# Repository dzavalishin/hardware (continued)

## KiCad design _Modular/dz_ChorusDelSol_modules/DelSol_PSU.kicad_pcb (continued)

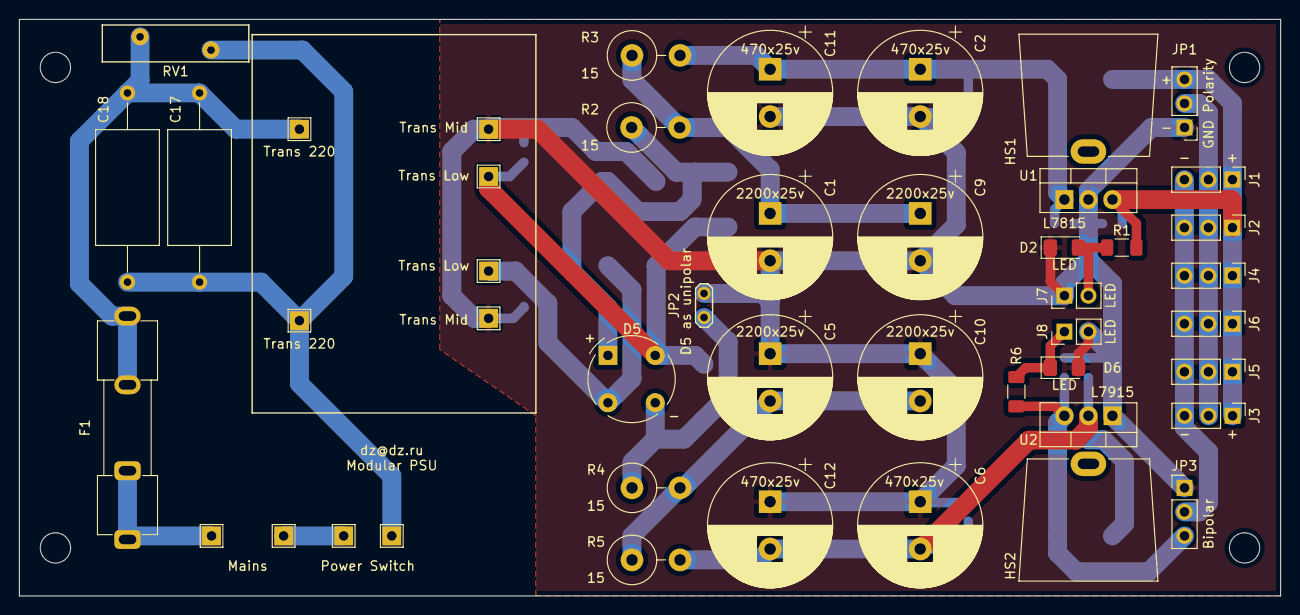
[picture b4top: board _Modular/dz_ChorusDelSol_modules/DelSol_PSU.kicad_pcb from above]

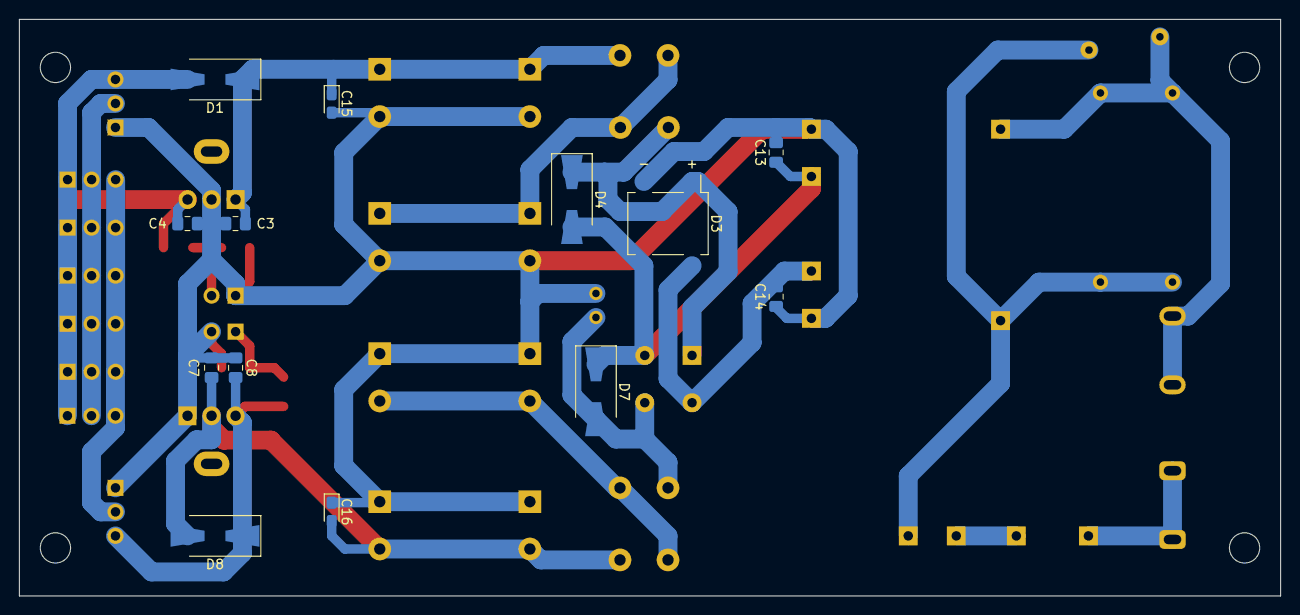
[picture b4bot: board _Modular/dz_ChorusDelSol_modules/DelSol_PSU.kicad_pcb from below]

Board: 2 copper layers, 133.3 x 61.0 mm, 63 parts (13 on the bottom side), 19 nets.

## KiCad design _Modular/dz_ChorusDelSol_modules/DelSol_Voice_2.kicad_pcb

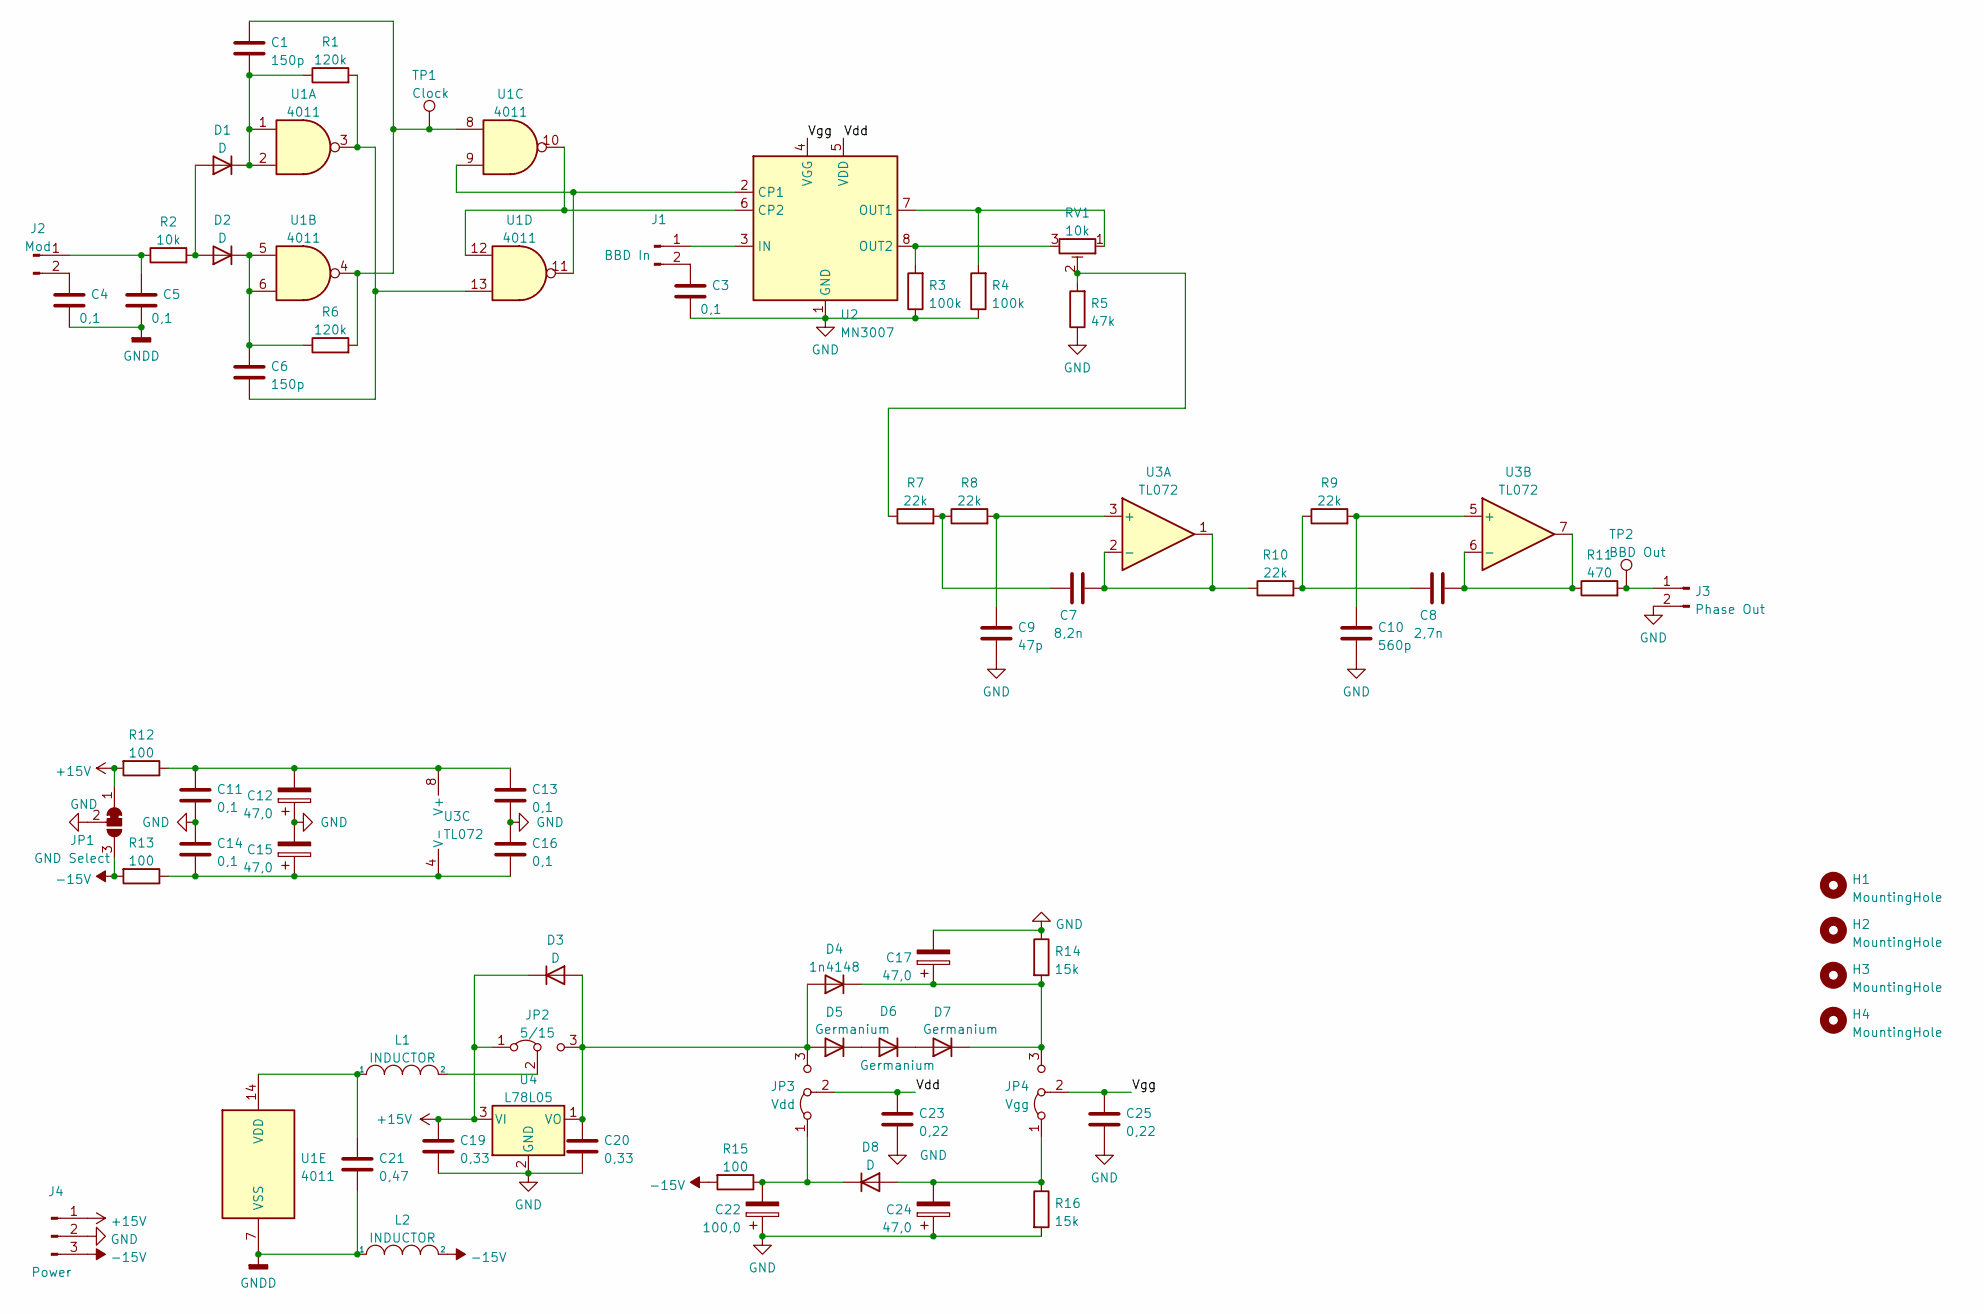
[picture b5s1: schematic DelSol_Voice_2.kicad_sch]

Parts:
C1, C6: 150p; C_Disc_D5.0mm_W2.5mm_P2.50mm
C3, C4, C5, C11, C13, C14, C16: 0,1; C_1206_3216Metric_Pad1.33x1.80mm_HandSolder
C7: 8,2n; C_Disc_D5.0mm_W2.5mm_P2.50mm
C8: 2,7n; C_Disc_D5.0mm_W2.5mm_P2.50mm
C9: 47p; C_Disc_D5.0mm_W2.5mm_P2.50mm
C10: 560p; C_Disc_D5.0mm_W2.5mm_P2.50mm
C12, C15, C17, C24: 47,0; C_Elec_6.3x5.8
C19, C20: 0,33; C_0805_2012Metric_Pad1.18x1.45mm_HandSolder
C21: 0,47; C_0805_2012Metric_Pad1.18x1.45mm_HandSolder
C22: 100,0; C_Elec_6.3x5.8
C23, C25: 0,22; C_0805_2012Metric_Pad1.18x1.45mm_HandSolder
D1, D2, D3, D8: D; D_MiniMELF_Handsoldering
D4: 1n4148; D_MiniMELF_Handsoldering
D5, D6, D7: Germanium; D_A-405_P2.54mm_Vertical_KathodeUp
H1, H2, H3, H4: MountingHole; MountingHole_3.2mm_M3
J1: BBD In; PinHeader_1x02_P2.54mm_Vertical
J2: Mod; PinHeader_1x02_P2.54mm_Vertical
J3: Phase Out; PinHeader_1x02_P2.54mm_Vertical
J4: Power; PinHeader_1x03_P2.54mm_Vertical
JP1: GND Select; PinHeader_1x03_P2.54mm_Vertical
JP2: 5/15; PinHeader_1x03_P2.54mm_Vertical
JP3: Vdd; PinHeader_1x03_P2.54mm_Vertical
JP4: Vgg; PinHeader_1x03_P2.54mm_Vertical
L1, L2: INDUCTOR; L_Radial_D10.0mm_P5.00mm_Fastron_07P
R1, R6: 120k; R_1206_3216Metric_Pad1.30x1.75mm_HandSolder
R2: 10k; R_1206_3216Metric_Pad1.30x1.75mm_HandSolder
R3, R4: 100k; R_1206_3216Metric_Pad1.30x1.75mm_HandSolder
R5: 47k; R_1206_3216Metric_Pad1.30x1.75mm_HandSolder
R7, R8, R9, R10: 22k; R_1206_3216Metric_Pad1.30x1.75mm_HandSolder
R11: 470; R_1206_3216Metric_Pad1.30x1.75mm_HandSolder
R12, R13, R15: 100; R_1206_3216Metric_Pad1.30x1.75mm_HandSolder
R14, R16: 15k; R_1206_3216Metric_Pad1.30x1.75mm_HandSolder
RV1: 10k; Potentiometer_Runtron_RM-065_Vertical
TP1: Clock; PinHeader_1x01_P2.54mm_Vertical
TP2: BBD Out; PinHeader_1x01_P2.54mm_Vertical
U1: 4011; DIP-14_W7.62mm
U2: MN3007; DIP-8_W7.62mm
U3: TL072; DIP-8_W7.62mm_Socket_LongPads
U4: L78L05; TO-92_Inline

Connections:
+15V: C19.1, D3.1 (K), J4.1, JP1.1 (A), JP2.1 (A), R12.2, U4.3 (VI)
-15V: J4.3, JP1.3 (B), L2.2, R13.2, R15.2
/Vdd: C23.1, JP3.2 (C), U2.5 (VDD)
/Vgg: C25.1, JP4.2 (C), U2.4 (VGG)
GND: C3.2, C9.1, C10.1, C11.2, C12.1, C13.2, C14.1, C15.2, C16.1, C17.2, C19.2, C20.2, C22.1, C23.2, C24.1, C25.2, J3.2, J4.2, JP1.2 (C), R3.1, R4.1, R5.1, R14.1, R16.2, U2.1 (GND), U4.2 (GND)
GNDD: C4.2, C5.2, C21.2, L2.1, U1.7 (VSS)
unnamed: C1.1, R6.2, TP1.1, U1.4, U1.8
unnamed: C1.2, D1.1 (K), R1.1, U1.1, U1.2
unnamed: C3.1, J1.2
unnamed: C4.1, J2.2
unnamed: C5.1, J2.1, R2.1
unnamed: C6.1, D2.1 (K), R6.1, U1.5, U1.6
unnamed: C6.2, R1.2, U1.3, U1.13
unnamed: C7.1, R7.2, R8.1
unnamed: C7.2, R10.1, U3.1, U3.2 (-)
unnamed: C8.1, R9.1, R10.2
unnamed: C8.2, R11.1, U3.6 (-), U3.7
unnamed: C9.2, R8.2, U3.3 (+)
unnamed: C10.2, R9.2, U3.5 (+)
unnamed: C11.1, C12.2, C13.1, R12.1, U3.8 (V+)
unnamed: C14.2, C15.1, C16.2, R13.1, U3.4 (V-)
unnamed: C17.1, D4.1 (K), D7.1 (K), JP4.3 (B), R14.2
unnamed: C20.1, D3.2 (A), D4.2 (A), D5.2 (A), JP2.3 (B), JP3.3 (B), U4.1 (VO)
unnamed: C21.1, L1.1, U1.14 (VDD)
unnamed: C22.2, D8.1 (K), JP3.1 (A), R15.1
unnamed: C24.2, D8.2 (A), JP4.1 (A), R16.1
unnamed: D1.2 (A), D2.2 (A), R2.2
unnamed: D5.1 (K), D6.2 (A)
unnamed: D6.1 (K), D7.2 (A)
unnamed: J1.1, U2.3 (IN)
unnamed: J3.1, R11.2, TP2.1
unnamed: JP2.2 (C), L1.2
unnamed: R3.2, RV1.3, U2.8 (OUT2)
unnamed: R4.2, RV1.1, U2.7 (OUT1)
unnamed: R5.2, R7.1, RV1.2
unnamed: U1.10, U1.12, U2.6 (CP2)
unnamed: U1.9, U1.11, U2.2 (CP1)

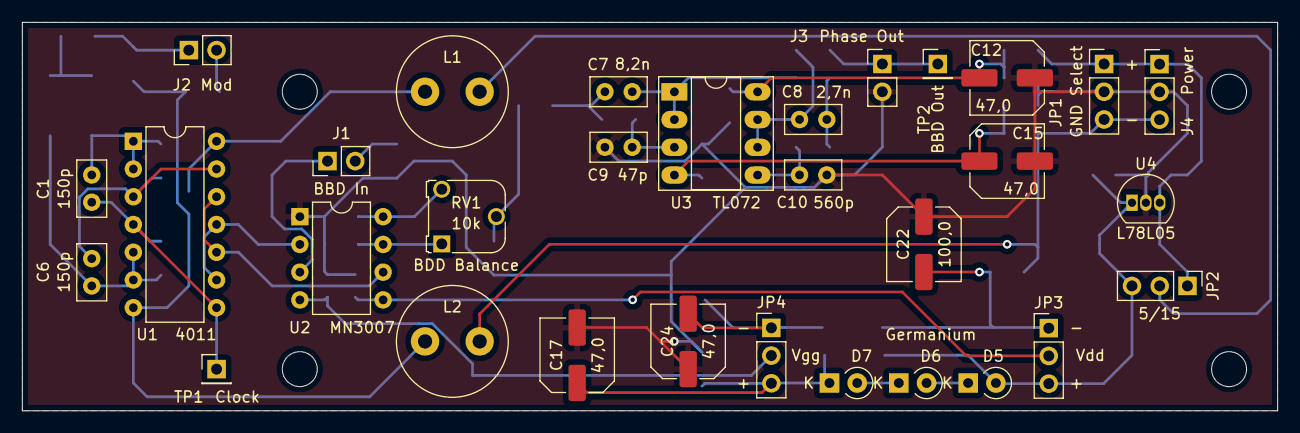
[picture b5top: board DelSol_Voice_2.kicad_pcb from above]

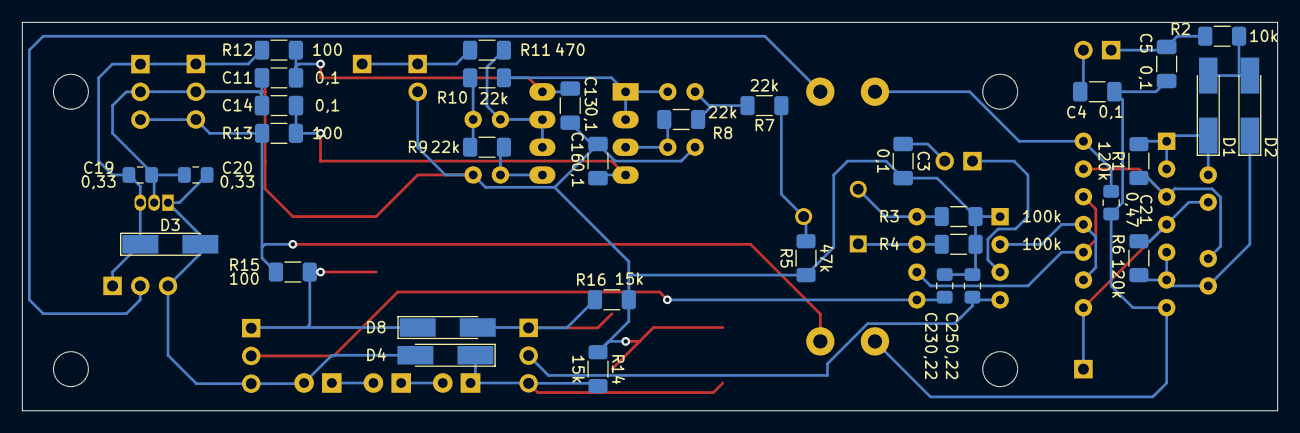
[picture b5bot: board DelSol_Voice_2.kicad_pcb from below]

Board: 2 copper layers, 114.9 x 35.6 mm, 68 parts (33 on the bottom side), 37 nets.

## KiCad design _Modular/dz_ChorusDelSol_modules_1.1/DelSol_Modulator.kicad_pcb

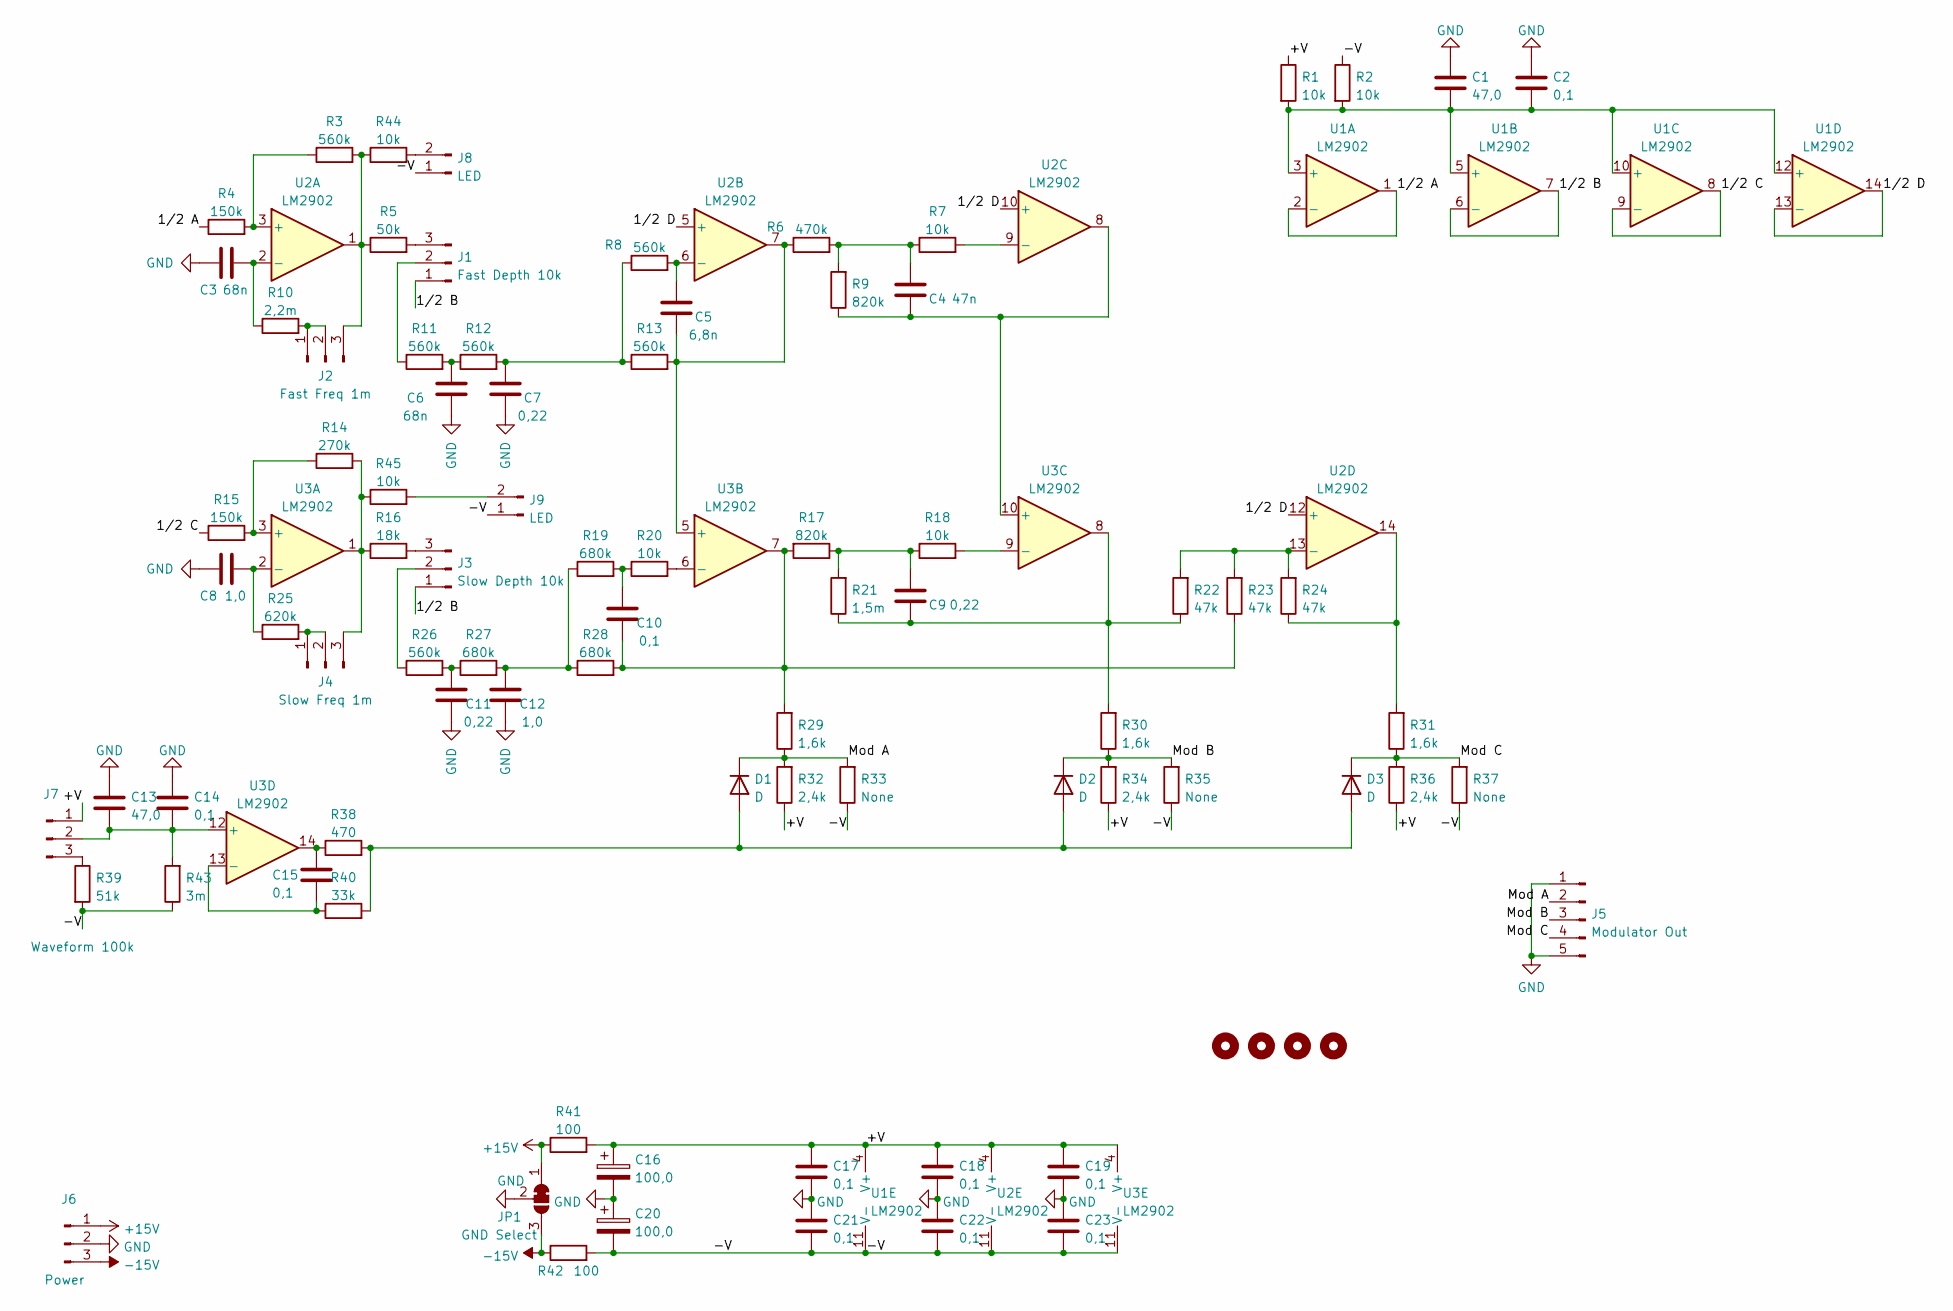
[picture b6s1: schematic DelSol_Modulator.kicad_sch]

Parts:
C1, C13: 47,0; C_Elec_6.3x5.8
C2, C10, C14, C15, C17, C18, C19, C21, C22, C23: 0,1; C_1206_3216Metric_Pad1.33x1.80mm_HandSolder
C3, C6: 68n; C_0805_2012Metric_Pad1.18x1.45mm_HandSolder
C4: 47n; C_0805_2012Metric_Pad1.18x1.45mm_HandSolder
C5: 6,8n; C_0805_2012Metric_Pad1.18x1.45mm_HandSolder
C7, C9, C11: 0,22; C_0805_2012Metric_Pad1.18x1.45mm_HandSolder
C8, C12: 1,0; C_0805_2012Metric_Pad1.18x1.45mm_HandSolder
C16, C20: 100,0; C_Elec_6.3x5.8
D1, D2, D3: D; D_MiniMELF_Handsoldering
H1, H2, H3, H4: MountingHole; MountingHole_3.2mm_M3
J1: Fast Depth 10k; PinHeader_1x03_P2.54mm_Vertical
J2: Fast Freq 1m; PinHeader_1x03_P2.54mm_Vertical
J3: Slow Depth 10k; PinHeader_1x03_P2.54mm_Vertical
J4: Slow Freq 1m; PinHeader_1x03_P2.54mm_Vertical
J5: Modulator Out; PinHeader_1x05_P2.54mm_Vertical
J6: Power; PinHeader_1x03_P2.54mm_Vertical
J7: Waveform 100k; PinHeader_1x03_P2.54mm_Vertical
J8, J9: LED; PinHeader_1x02_P2.54mm_Vertical
JP1: GND Select; PinHeader_1x03_P2.54mm_Vertical
R1, R2, R7, R18, R20, R44, R45: 10k; R_1206_3216Metric_Pad1.30x1.75mm_HandSolder
R3, R8, R11, R12, R13, R26: 560k; R_1206_3216Metric_Pad1.30x1.75mm_HandSolder
R4, R15: 150k; R_1206_3216Metric_Pad1.30x1.75mm_HandSolder
R5: 50k; R_1206_3216Metric_Pad1.30x1.75mm_HandSolder
R6: 470k; R_1206_3216Metric_Pad1.30x1.75mm_HandSolder
R9, R17: 820k; R_1206_3216Metric_Pad1.30x1.75mm_HandSolder
R10: 2,2m; R_1206_3216Metric_Pad1.30x1.75mm_HandSolder
R14: 270k; R_1206_3216Metric_Pad1.30x1.75mm_HandSolder
R16: 18k; R_1206_3216Metric_Pad1.30x1.75mm_HandSolder
R19, R27, R28: 680k; R_1206_3216Metric_Pad1.30x1.75mm_HandSolder
R21: 1,5m; R_1206_3216Metric_Pad1.30x1.75mm_HandSolder
R22, R23, R24: 47k; R_1206_3216Metric_Pad1.30x1.75mm_HandSolder
R25: 620k; R_1206_3216Metric_Pad1.30x1.75mm_HandSolder
R29, R30, R31: 1,6k; R_1206_3216Metric_Pad1.30x1.75mm_HandSolder
R32, R34, R36: 2,4k; R_1206_3216Metric_Pad1.30x1.75mm_HandSolder
R33, R35, R37: None; R_1206_3216Metric_Pad1.30x1.75mm_HandSolder
R38: 470; R_1206_3216Metric_Pad1.30x1.75mm_HandSolder
R39: 51k; R_1206_3216Metric_Pad1.30x1.75mm_HandSolder
R40: 33k; R_1206_3216Metric_Pad1.30x1.75mm_HandSolder
R41, R42: 100; R_1206_3216Metric_Pad1.30x1.75mm_HandSolder
R43: 3m; R_1206_3216Metric_Pad1.30x1.75mm_HandSolder
U1, U2, U3: LM2902; DIP-14_W7.62mm

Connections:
+15V: J6.1, JP1.1 (A), R41.1
-15V: J6.3, JP1.3 (B), R42.1
/1/2 A: R4.1, U1.1, U1.2 (-)
/1/2 B: J1.1, J3.1, U1.6 (-), U1.7
/1/2 C: R15.1, U1.8, U1.9 (-)
/1/2 D: U1.13 (-), U1.14, U2.5 (+), U2.10 (+), U2.12 (+)
/+V: C16.1, C17.1, C18.1, C19.1, J7.1, R1.1, R32.1, R34.1, R36.1, R41.2, U1.4 (V+), U2.4 (V+), U3.4 (V+)
/-V: C20.2, C21.2, C22.2, C23.2, J8.1, J9.1, R2.1, R33.1, R35.1, R37.1, R39.2, R42.2, R43.1, U1.11 (V-), U2.11 (V-), U3.11 (V-)
/Mod A: D1.1 (K), J5.2, R29.1, R32.2, R33.2
/Mod B: D2.1 (K), J5.3, R30.1, R34.2, R35.2
/Mod C: D3.1 (K), J5.4, R31.1, R36.2, R37.2
GND: C1.1, C2.1, C3.1, C6.1, C7.1, C8.1, C11.1, C12.1, C13.1, C14.1, C16.2, C17.2, C18.2, C19.2, C20.1, C21.1, C22.1, C23.1, J5.1, J5.5, J6.2, JP1.2 (C)
unnamed: C1.2, C2.2, R1.2, R2.2, U1.3 (+), U1.5 (+), U1.10 (+), U1.12 (+)
unnamed: C3.2, R10.1, U2.2 (-)
unnamed: C4.1, R9.1, U2.8, U3.10 (+)
unnamed: C4.2, R6.2, R7.1, R9.2
unnamed: C5.1, R6.1, R13.2, U2.7, U3.5 (+)
unnamed: C5.2, R8.2, U2.6 (-)
unnamed: C6.2, R11.2, R12.1
unnamed: C7.2, R8.1, R12.2, R13.1
unnamed: C8.2, R25.1, U3.2 (-)
unnamed: C9.1, R21.1, R22.1, R30.2, U3.8
unnamed: C9.2, R17.1, R18.1, R21.2
unnamed: C10.1, R17.2, R23.1, R28.2, R29.2, U3.7
unnamed: C10.2, R19.2, R20.1
unnamed: C11.2, R26.2, R27.1
unnamed: C12.2, R19.1, R27.2, R28.1
unnamed: C13.2, C14.2, J7.2, R43.2, U3.12 (+)
unnamed: C15.1, R38.1, U3.14
unnamed: C15.2, R40.1, U3.13 (-)
unnamed: D1.2 (A), D2.2 (A), D3.2 (A), R38.2, R40.2
unnamed: J1.2, R11.1
unnamed: J1.3, R5.2
unnamed: J2.1, J2.2, R10.2
unnamed: J2.3, R3.2, R5.1, R44.1, U2.1
unnamed: J3.2, R26.1
unnamed: J3.3, R16.2
unnamed: J4.1, J4.2, R25.2
unnamed: J4.3, R14.2, R16.1, R45.1, U3.1
unnamed: J8.2, R44.2
unnamed: J9.2, R45.2
unnamed: R3.1, R4.2, U2.3 (+)
unnamed: R7.2, U2.9 (-)
unnamed: R14.1, R15.2, U3.3 (+)
unnamed: R18.2, U3.9 (-)
unnamed: R20.2, U3.6 (-)
unnamed: R22.2, R23.2, R24.2, U2.13 (-)
unnamed: R24.1, R31.2, U2.14
unnamed: J7.3, R39.1

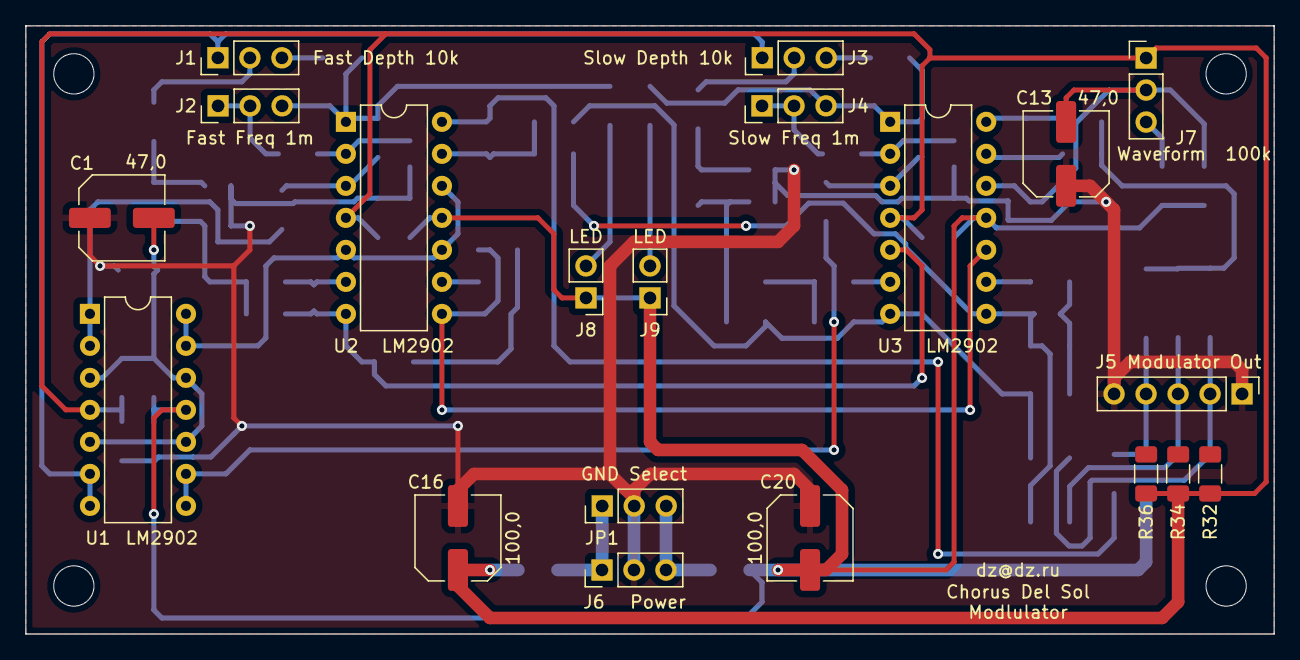
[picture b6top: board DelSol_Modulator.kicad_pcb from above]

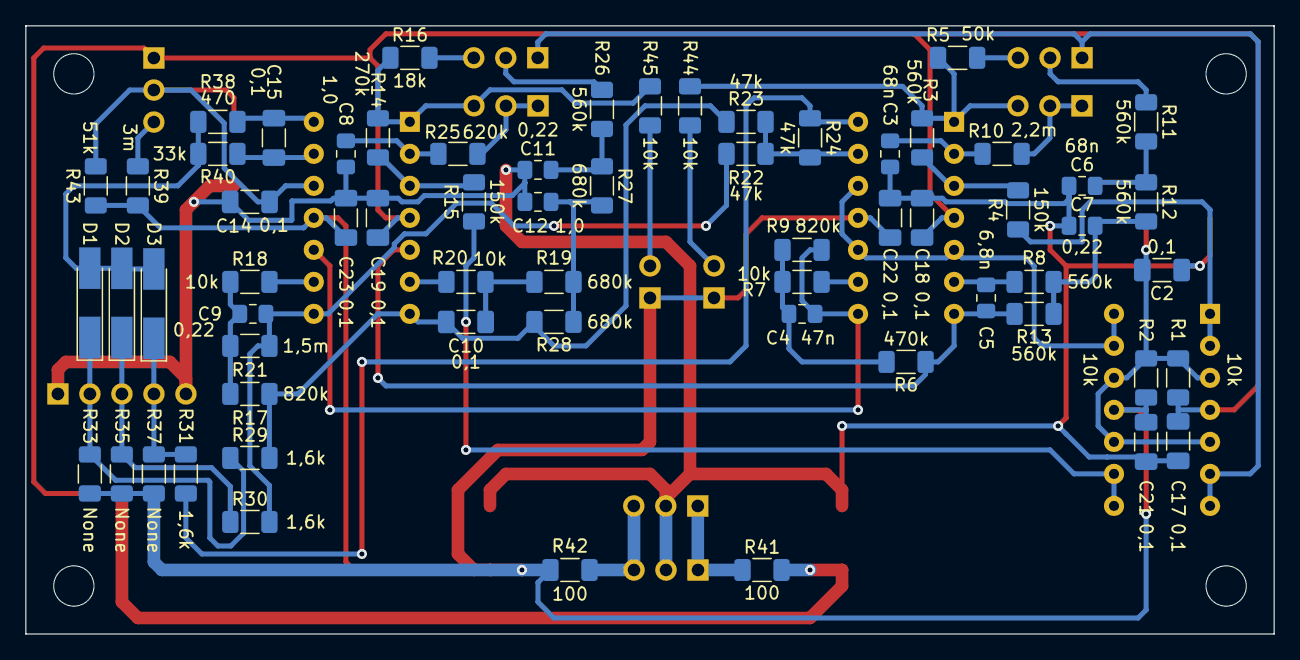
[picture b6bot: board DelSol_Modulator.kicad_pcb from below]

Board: 2 copper layers, 99.1 x 48.3 mm, 88 parts (64 on the bottom side), 49 nets.

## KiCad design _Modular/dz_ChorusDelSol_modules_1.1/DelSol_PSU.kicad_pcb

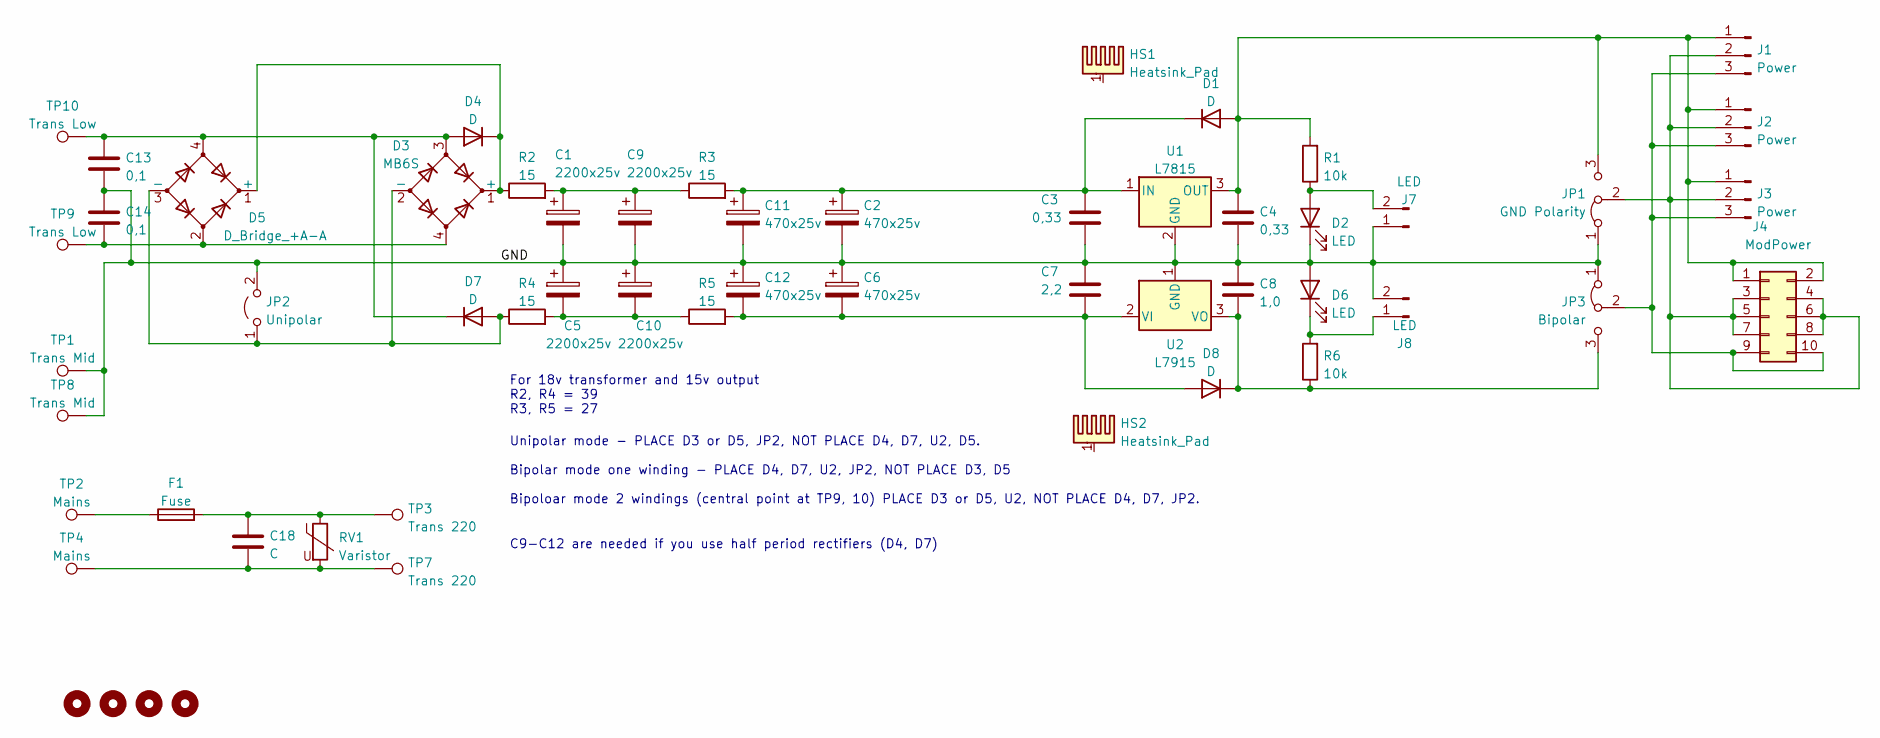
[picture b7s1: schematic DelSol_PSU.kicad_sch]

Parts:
C1, C5, C9, C10: 2200x25v; CP_Radial_D13.0mm_P5.00mm
C2, C6, C11, C12: 470x25v; CP_Radial_D13.0mm_P5.00mm
C3, C4: 0,33; C_0805_2012Metric_Pad1.18x1.45mm_HandSolder
C7: 2,2; C_0805_2012Metric_Pad1.18x1.45mm_HandSolder
C8: 1,0; C_0805_2012Metric_Pad1.18x1.45mm_HandSolder
C13, C14: 0,1; C_Rect_L13.0mm_W6.0mm_P10.00mm_FKS3_FKP3_MKS4
C18: C; C_Rect_L13.0mm_W6.0mm_P10.00mm_FKS3_FKP3_MKS4
D1, D4, D7, D8: D; D_SMA-SMB_Universal_Handsoldering
D2, D6: LED; LED_1206_3216Metric_Pad1.42x1.75mm_HandSolder
D3: MB6S; TO-269AA
D5: D_Bridge_+A-A; Diode_Bridge_Round_D9.0mm
F1: Fuse; Fuseholder_Clip-5x20mm_Keystone_3512_Inline_P23.62x7.27mm_D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
H1, H2, H3, H4: MountingHole; MountingHole_3.2mm_M3
HS1, HS2: Heatsink_Pad; Heatsink_TO_220
J1, J2, J3: Power; PinHeader_1x03_P2.54mm_Vertical
J4: ModPower; PinHeader_2x05_P2.54mm_Vertical
J7, J8: LED; PinHeader_1x02_P2.54mm_Vertical
JP1: GND Polarity; PinHeader_1x03_P2.54mm_Vertical
JP2: Unipolar; TestPoint_2Pads_Pitch2.54mm_Drill0.8mm
JP3: Bipolar; PinHeader_1x03_P2.54mm_Vertical
R1, R6: 10k; R_1206_3216Metric_Pad1.30x1.75mm_HandSolder
R2, R3, R4, R5: 15; R_Axial_DIN0516_L15.5mm_D5.0mm_P5.08mm_Vertical
RV1: Varistor; RV_Disc_D15.5mm_W3.9mm_P7.5mm
TP1, TP8: Trans Mid; TestPoint_THTPad_3.0x3.0mm_Drill1.5mm
TP2, TP4: Mains; TestPoint_THTPad_2.0x2.0mm_Drill1.0mm
TP3, TP7: Trans 220; TestPoint_THTPad_3.0x3.0mm_Drill1.5mm
TP9, TP10: Trans Low; TestPoint_THTPad_3.0x3.0mm_Drill1.5mm
U1: L7815; TO-220-3_Vertical
U2: L7915; TO-220-3_Vertical

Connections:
/GND: C1.2, C2.2, C3.2, C4.2, C5.1, C6.1, C7.1, C8.1, C9.2, C10.1, C11.2, C12.1, C13.2, C14.1, D2.1 (K), D6.2 (A), J7.1, J8.2, JP1.1 (A), JP2.2 (B), JP3.1 (A), TP1.1, TP8.1, U1.2 (GND), U2.1 (GND)
unnamed: C1.1, C9.1, R2.2, R3.1
unnamed: C4.1, D1.2 (A), J1.1, J2.1, J3.1, J4.1, J4.2, JP1.3 (B), R1.2, U1.3 (OUT)
unnamed: C8.2, D8.1 (K), JP3.3 (B), R6.1, U2.3 (VO)
unnamed: C5.2, C10.2, R4.2, R5.1
unnamed: C2.1, C3.1, C11.1, D1.1 (K), R3.2, U1.1 (IN)
unnamed: C6.2, C7.2, C12.2, D8.2 (A), R5.2, U2.2 (VI)
unnamed: C13.1, D3.3, D4.2 (A), D5.4, D7.1 (K), TP10.1
unnamed: C14.2, D3.4, D5.2, TP9.1
unnamed: C18.1, F1.2, RV1.1, TP3.1
unnamed: C18.2, RV1.2, TP4.1, TP7.1
unnamed: D2.2 (A), J7.2, R1.1
unnamed: D3.1 (+), D4.1 (K), D5.1 (+), R2.1
unnamed: D3.2 (-), D5.3 (-), D7.2 (A), JP2.1 (A), R4.1
unnamed: D6.1 (K), J8.1, R6.2
unnamed: F1.1, TP2.1
unnamed: J1.2, J2.2, J3.2, J4.3, J4.4, J4.5, J4.6, J4.7, J4.8, JP1.2 (C)
unnamed: J1.3, J2.3, J3.3, J4.9, J4.10, JP3.2 (C)

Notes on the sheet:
Unipolar mode - PLACE D3 or D5, JP2, NOT PLACE D4, D7, U2, D5. Bipolar mode one winding - PLACE D4, D7, U2, JP2, NOT PLACE D3, D5 Bipoloar mode 2 windings (central point at TP9, 10) PLACE D3 or D5, U2, NOT PLACE D4, D7, JP2.
C9-C12 are needed if you use half period rectifiers (D4, D7)
For 18v transformer and 15v output R2, R4 = 39 R3, R5 = 27

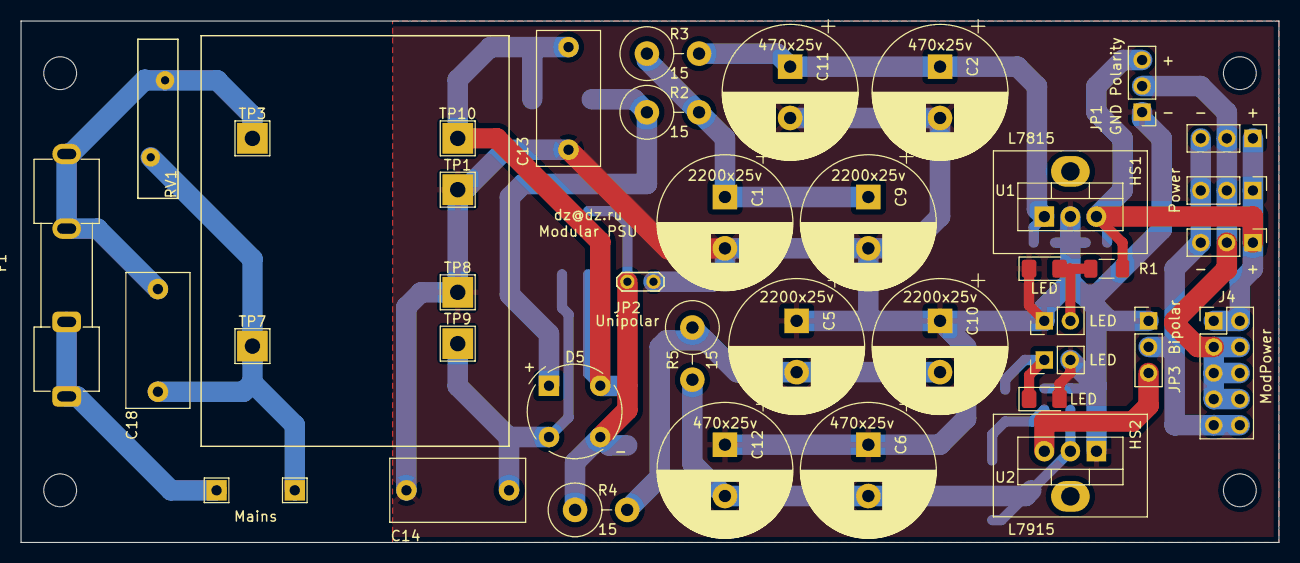
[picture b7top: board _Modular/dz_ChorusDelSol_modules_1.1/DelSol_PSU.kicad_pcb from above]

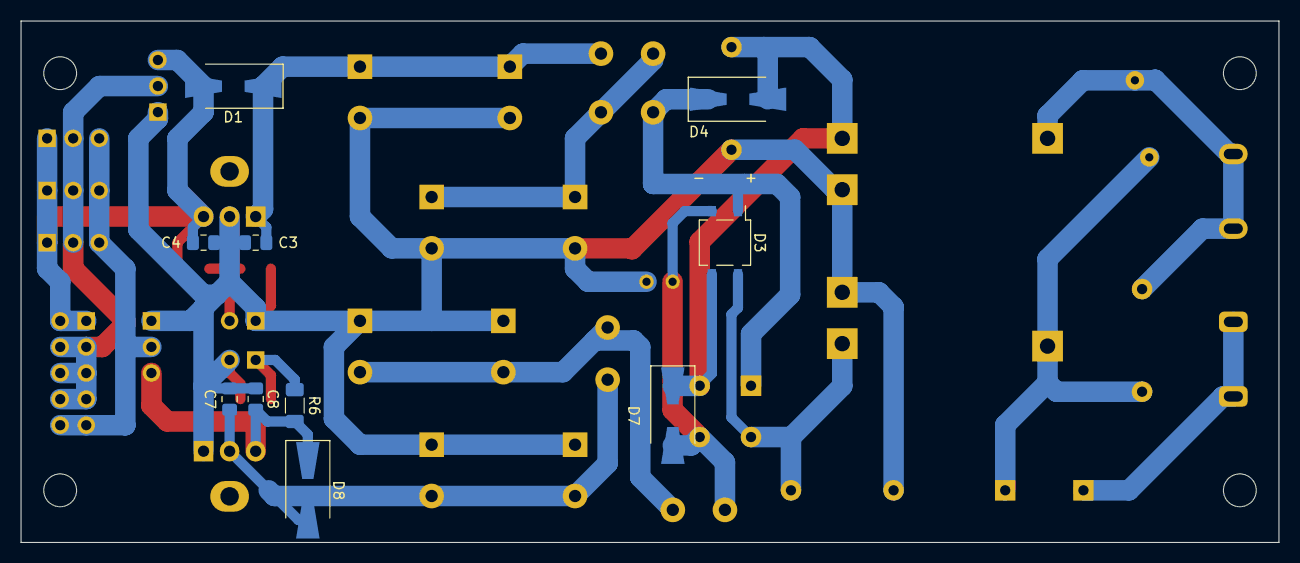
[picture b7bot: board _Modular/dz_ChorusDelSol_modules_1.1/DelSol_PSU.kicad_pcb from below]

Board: 2 copper layers, 122.6 x 50.8 mm, 56 parts (10 on the bottom side), 18 nets.
